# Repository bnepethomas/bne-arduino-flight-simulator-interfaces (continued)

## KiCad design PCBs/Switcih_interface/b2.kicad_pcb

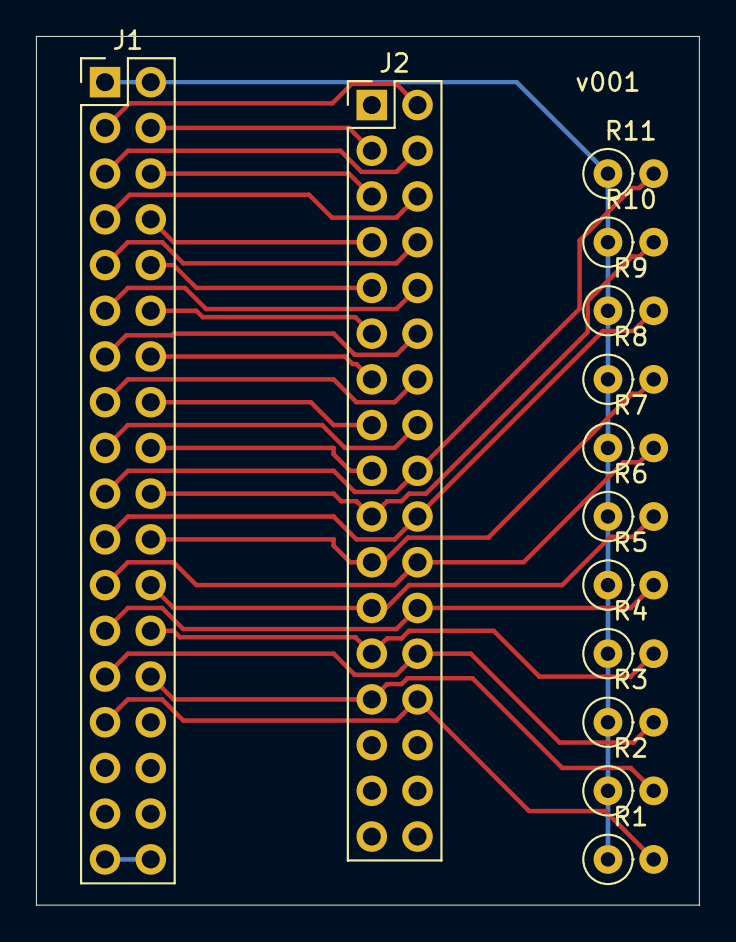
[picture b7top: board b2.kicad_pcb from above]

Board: 2 copper layers, 36.8 x 48.3 mm, 13 parts (0 on the bottom side), 29 nets.

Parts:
J1: PinHeader_2x18_P2.54mm_Vertical
J2: PinHeader_2x17_P2.54mm_Vertical
R1: R_Axial_DIN0207_L6.3mm_D2.5mm_P2.54mm_Vertical
R2, R3, R4, R5, R6, R7, R8, R9, R10, R11: R_US; R_Axial_DIN0207_L6.3mm_D2.5mm_P2.54mm_Vertical

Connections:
+5V: J1.1, J1.2, R1.1, R2.1, R3.1, R4.1, R5.1, R6.1, R7.1, R8.1, R9.1, R10.1, R11.1
/Col0: J1.19, J2.18, R11.2
/Col1: J1.20, J2.19, R10.2
/Col2: J1.21, J2.20, R9.2
/Col3: J1.22, J2.21, R8.2
/Col4: J1.23, J2.22, R7.2
/Col5: J1.24, J2.23, R6.2
/Col6: J1.25, J2.24, R5.2
/Col7: J1.26, J2.25, R4.2
/Col8: J1.27, J2.26, R3.2
/Col9: J1.28, J2.27, R2.2
/Col10: J1.29, J2.28, R1.2
/Row0: J1.3, J2.2
/Row1: J1.4, J2.3
/Row2: J1.5, J2.4
/Row3: J1.6, J2.5
/Row4: J1.7, J2.6
/Row5: J1.8, J2.7
/Row6: J1.9, J2.8
/Row7: J1.10, J2.9
/Row8: J1.11, J2.10
/Row9: J1.12, J2.11
/Row10: J1.13, J2.12
/Row11: J1.14, J2.13
/Row12: J1.15, J2.14
/Row13: J1.16, J2.15
/Row14: J1.17, J2.16
/Row15: J1.18, J2.17
unnamed: J1.35, J1.36

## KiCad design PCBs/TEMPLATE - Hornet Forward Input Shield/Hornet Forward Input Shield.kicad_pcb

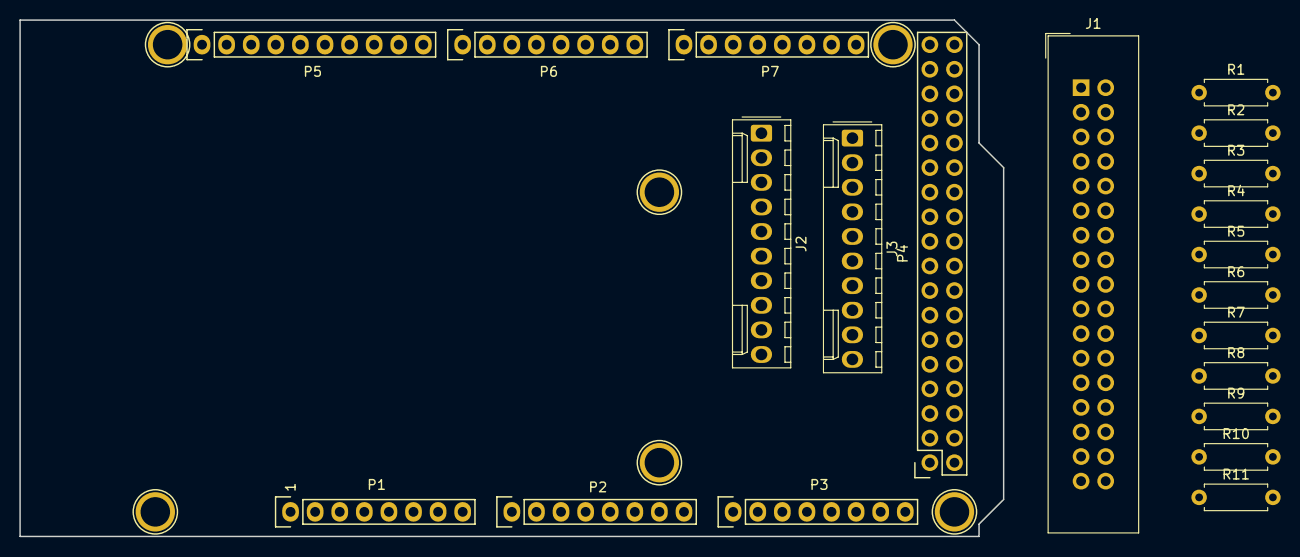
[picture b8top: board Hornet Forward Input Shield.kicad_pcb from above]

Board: 2 copper layers, 101.6 x 53.3 mm, 27 parts (0 on the bottom side), 45 nets, no tracks yet.

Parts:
J1: MATRIX INPUT; IDC-Header_2x17_P2.54mm_Vertical
J2: ANALOG B; Molex_1x10_P2.54mm_Vertical
J3: ENCODERS; Molex_1x10_P2.54mm_Vertical
P1: Power; Socket_Strip_Arduino_1x08
P2, P3: Analog; Socket_Strip_Arduino_1x08
P4: Digital; Socket_Strip_Arduino_2x18
P5: PWM; Socket_Strip_Arduino_1x10
P6: PWM; Socket_Strip_Arduino_1x08
P7: Communication; Socket_Strip_Arduino_1x08
P8, P9, P10, P11, P12, P13: CONN_01X01; Arduino_1pin
R1, R2, R3, R4, R5, R6, R7, R8, R9, R10, R11: R; R_Axial_DIN0207_L6.3mm_D2.5mm_P7.62mm_Horizontal

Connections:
+5V: J2.1, P1.5, P4.35, P4.36, R1.1, R2.1, R3.1, R4.1, R5.1, R6.1, R7.1, R8.1, R9.1, R10.1, R11.1
/14(Tx3): J3.2, P7.1
/15(Rx3): J3.3, P7.2
/16(Tx2): J3.4, P7.3
/17(Rx2): J3.5, P7.4
/18(Tx1): J3.6, P7.5
/19(Rx1): J3.7, P7.6
/20(SDA): J3.8, P7.7
/21(SCL): J3.9, P7.8
/22: J1.2, P4.33
/23: J1.3, P4.34
/24: J1.4, P4.31
/25: J1.5, P4.32
/26: J1.6, P4.29
/27: J1.7, P4.30
/28: J1.8, P4.27
/29: J1.9, P4.28
/30: J1.10, P4.25
/31: J1.11, P4.26
/32: J1.12, P4.23
/33: J1.13, P4.24
/34: J1.14, P4.21
/35: J1.15, P4.22
/36: J1.16, P4.19
/37: J1.17, P4.20
/38: J1.18, P4.17, R1.2
/39: J1.19, P4.18, R2.2
/40: J1.20, P4.15, R3.2
/41: J1.21, P4.16, R4.2
/42: J1.22, P4.13, R5.2
/43: J1.23, P4.14, R6.2
/44: J1.24, P4.11, R7.2
/45: J1.25, P4.12, R8.2
/46: J1.26, P4.9, R9.2
/47: J1.27, P4.10, R10.2
/48: J1.28, P4.7, R11.2
/A8: J2.3, P3.1
/A9: J2.4, P3.2
/A10: J2.5, P3.3
/A11: J2.6, P3.4
/A12: J2.7, P3.5
/A13: J2.8, P3.6
/A14: J2.9, P3.7
/A15: J2.10, P3.8
GND: J2.2, J3.1, P1.6, P1.7, P4.1, P4.2, P5.4
